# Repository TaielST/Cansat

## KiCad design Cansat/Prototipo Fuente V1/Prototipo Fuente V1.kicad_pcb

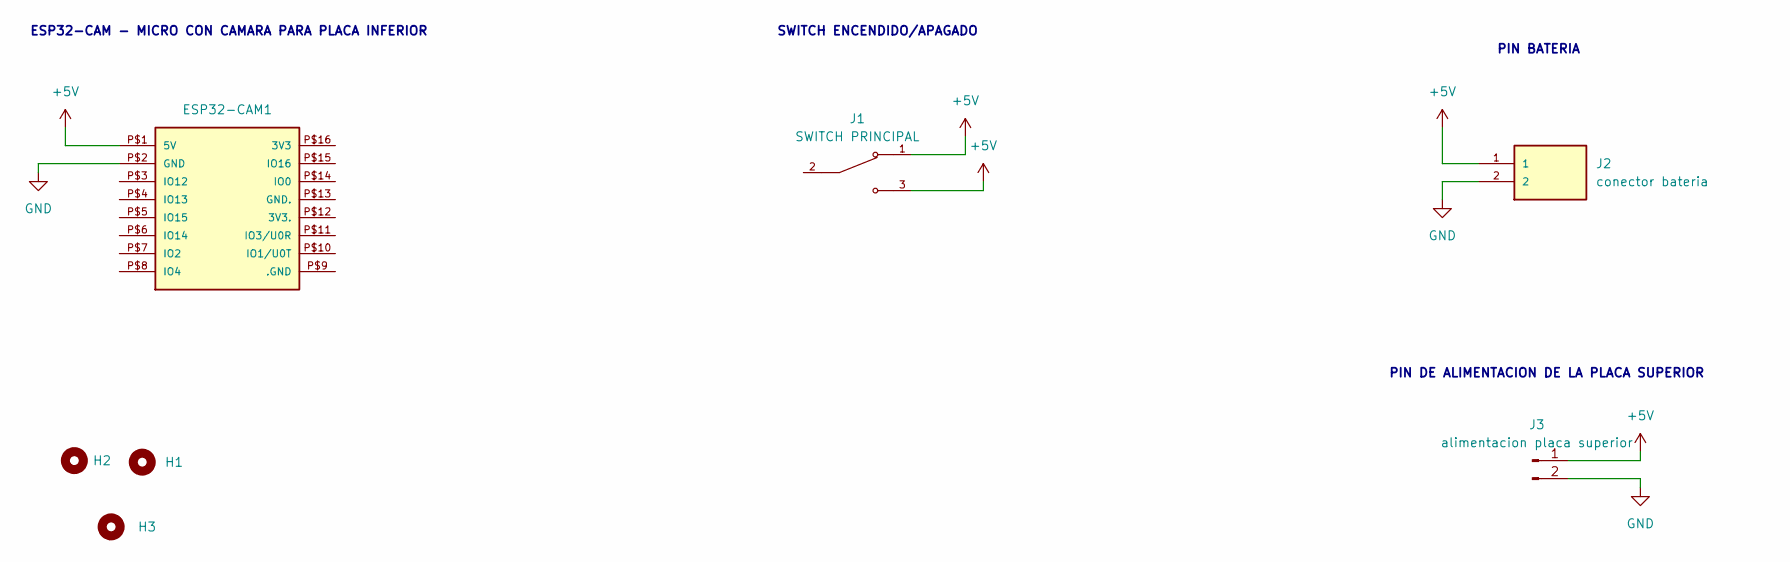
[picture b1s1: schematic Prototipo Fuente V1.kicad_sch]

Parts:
ESP32-CAM1: ESP32-CAM
H1, H2, H3: Mounting_Hole; hole_3mm
J1: SWITCH PRINCIPAL; SW_500SSP1S2M2QEA; PARTREV C
J2: conector bateria; TE_3-647630-2
J3: alimentacion placa superior; PinHeader_1x02_P2.54mm_Vertical

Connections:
+5V: ESP32-CAM1.P$1 (5V), J1.1, J1.3, J2.1, J3.1
GND: ESP32-CAM1.P$2 (GND), J2.2, J3.2

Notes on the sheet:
ESP32-CAM - MICRO CON CAMARA PARA PLACA INFERIOR
PIN DE ALIMENTACION DE LA PLACA SUPERIOR
PIN BATERIA
SWITCH ENCENDIDO/APAGADO

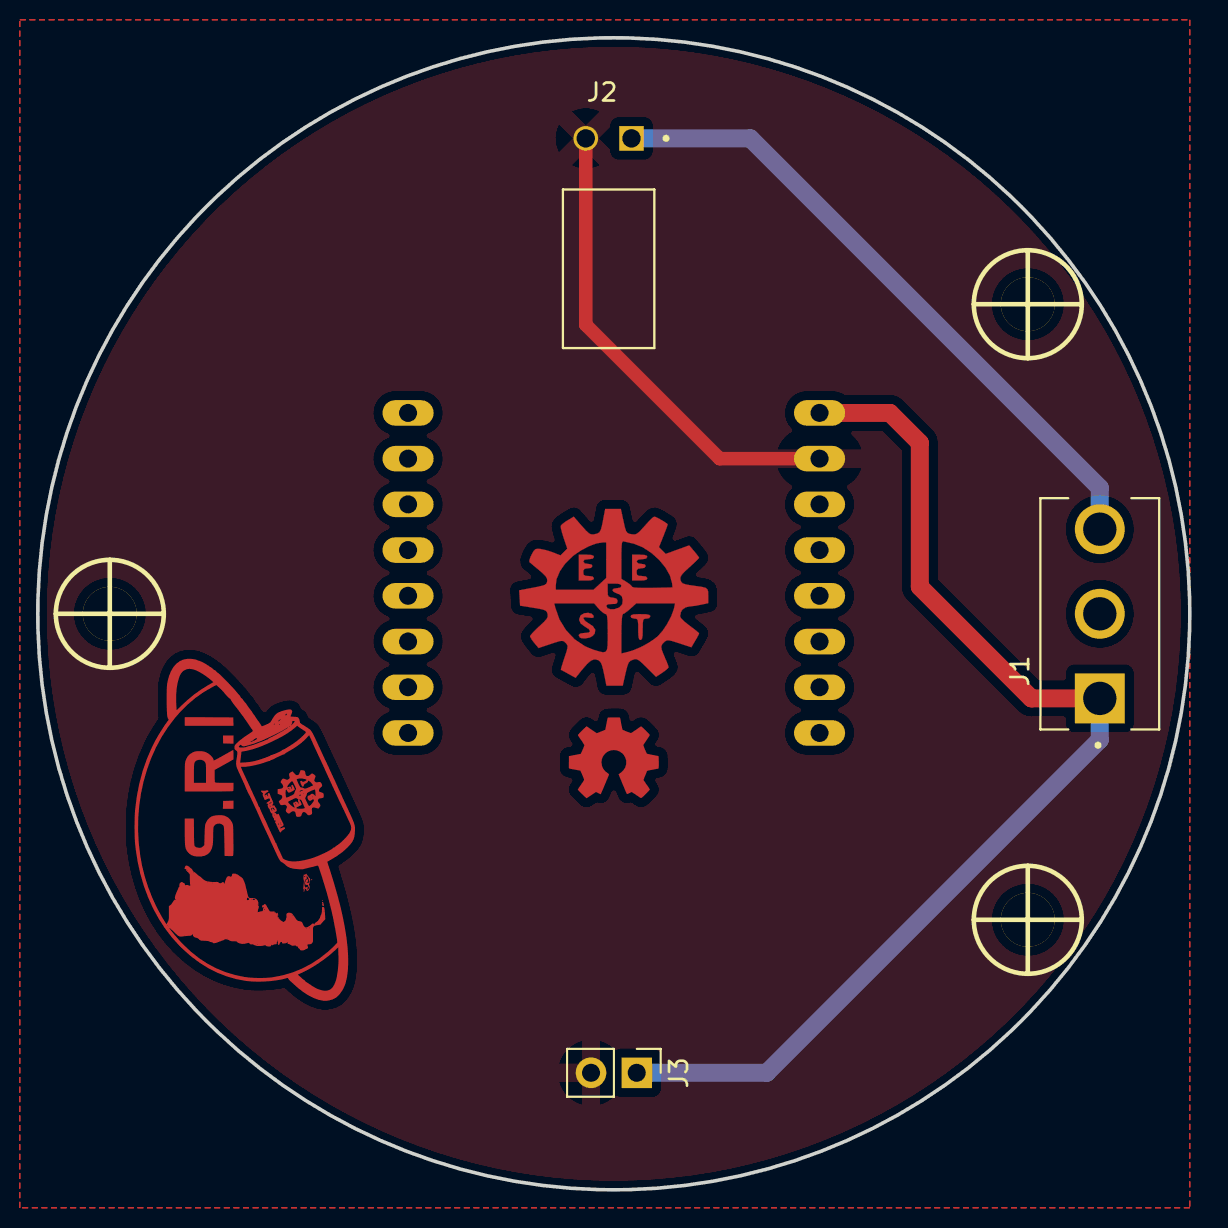
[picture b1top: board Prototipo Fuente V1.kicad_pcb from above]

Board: 2 copper layers, 64.0 x 64.0 mm, 8 parts (1 on the bottom side), 2 nets.

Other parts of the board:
H6: Mounting_Hole; Logo_OSHW_6x6mm_FCu
